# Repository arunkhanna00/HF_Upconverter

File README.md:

# Upconverter
An upconverter used to convert HF signals (3-33 MHz) to 125+MHz that can be recognized by an RTL-SDR

Inspired by [Nooelectric Ham It Up](https://www.nooelec.com/store/ham-it-up.html)

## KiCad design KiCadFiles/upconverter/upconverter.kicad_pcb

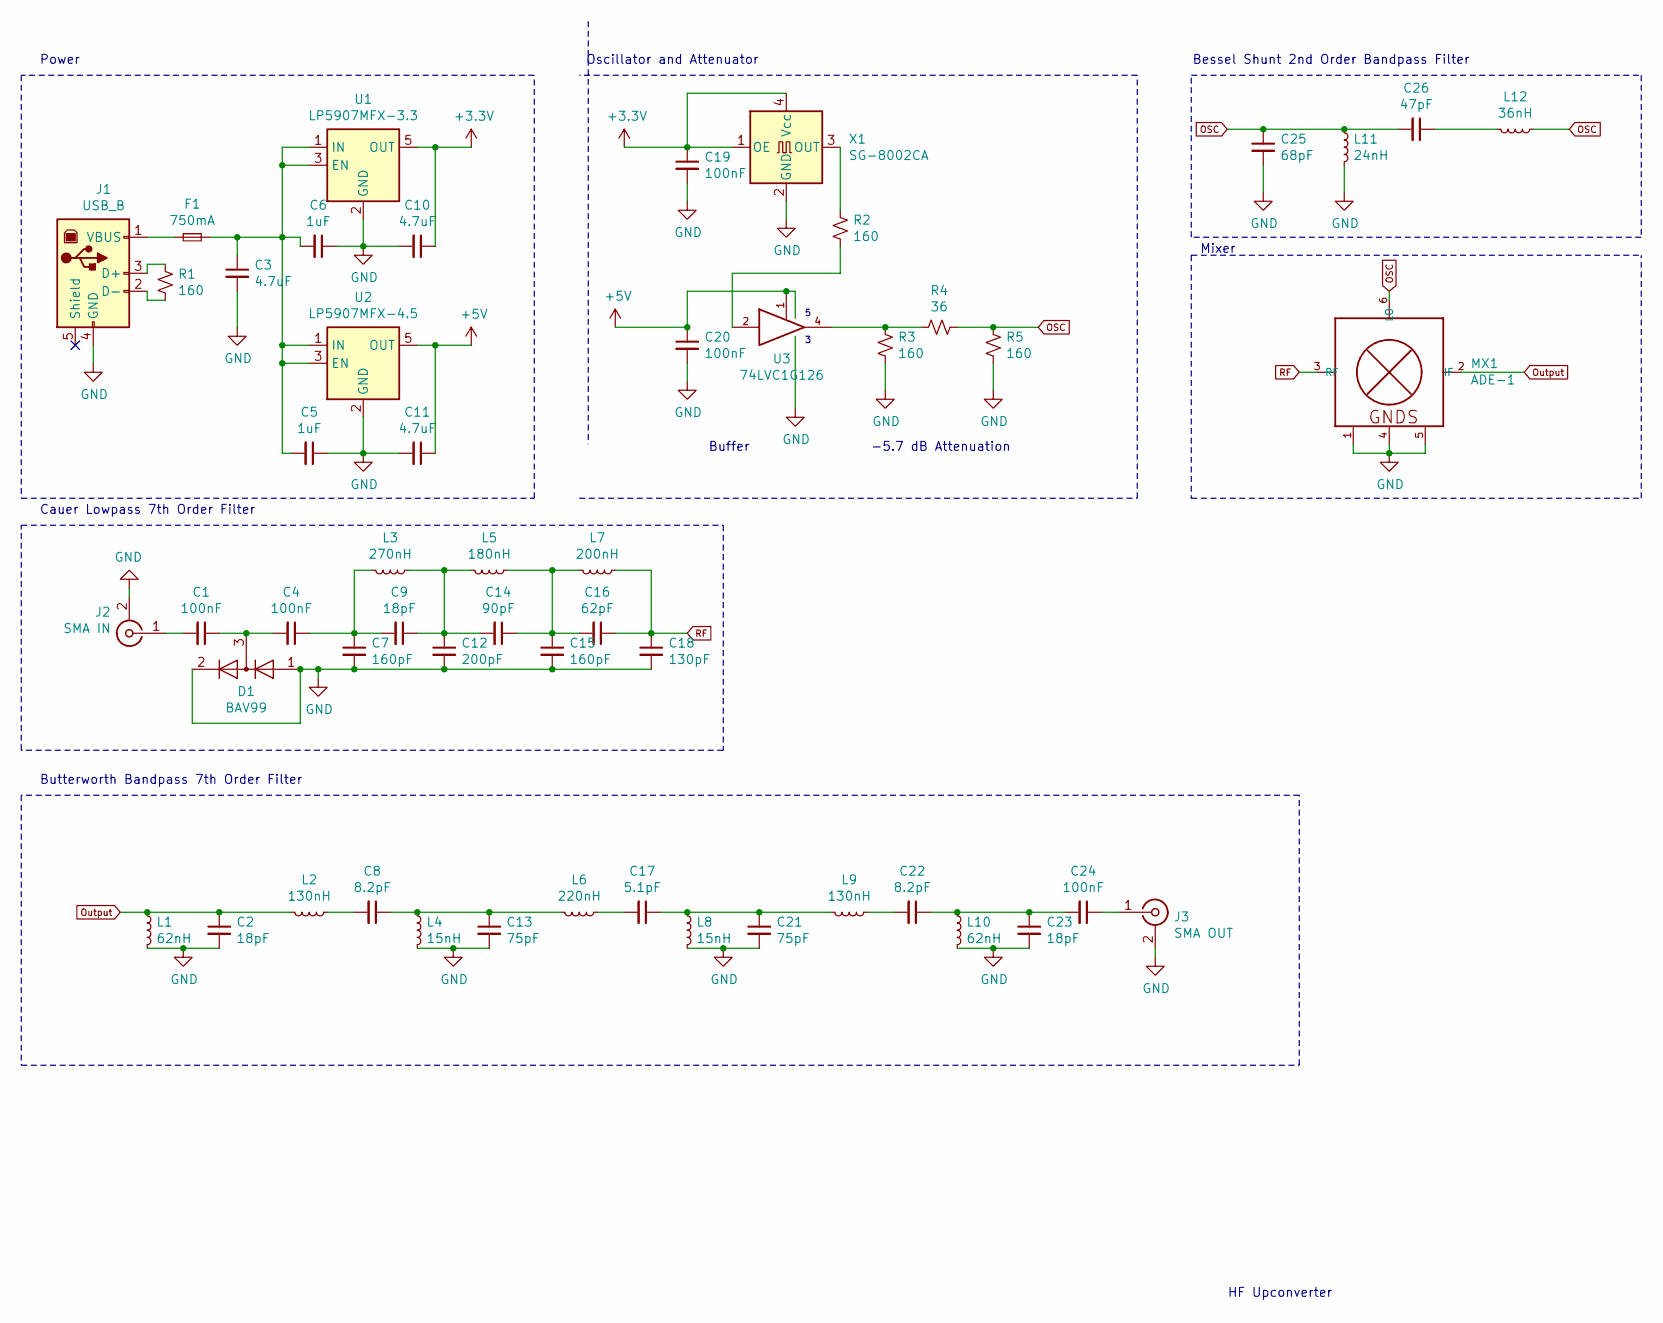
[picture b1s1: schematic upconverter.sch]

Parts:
C1, C4, C19, C20, C24: 100nF; C_0805_2012Metric
C2, C9, C23: 18pF; C_0805_2012Metric
C3, C10, C11: 4.7uF; C_0805_2012Metric
C5, C6: 1uF; C_0805_2012Metric
C7, C15: 160pF; C_0805_2012Metric
C8, C22: 8.2pF; C_0805_2012Metric
C12: 200pF; C_0805_2012Metric
C13, C21: 75pF; C_0805_2012Metric
C14: 90pF; C_0805_2012Metric
C16: 62pF; C_0805_2012Metric
C17: 5.1pF; C_0805_2012Metric
C18: 130pF; C_0805_2012Metric
C25: 68pF; C_0805_2012Metric
C26: 47pF; C_0805_2012Metric
D1: BAV99; SOT-23
F1: 750mA; Fuse_1206_3216Metric_Castellated
J1: USB_B; USB_B_OST_USB-B1HSxx_Horizontal
J2: SMA IN; SMA_Samtec_SMA-J-P-X-ST-EM1_EdgeMount
J3: SMA OUT; SMA_Samtec_SMA-J-P-X-ST-EM1_EdgeMount
L1, L10: 62nH; L_0805_2012Metric
L2, L9: 130nH; L_0805_2012Metric
L3: 270nH; L_0805_2012Metric
L4, L8: 15nH; L_0805_2012Metric
L5: 180nH; L_0805_2012Metric
L6: 220nH; L_0805_2012Metric
L7: 200nH; L_0805_2012Metric
L11: 24nH; L_0805_2012Metric
L12: 36nH; L_0805_2012Metric
MX1: ADE-1; CD636
R1, R2, R3, R5: 160; R_0805_2012Metric
R4: 36; R_0805_2012Metric
U1: LP5907MFX-3.3; SOT-23-5
U2: LP5907MFX-4.5; SOT-23-5
U3: 74LVC1G126; SOT-23-5
X1: SG-8002CA; Oscillator_SMD_SeikoEpson_SG8002CA-4Pin_7.0x5.0mm

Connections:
+3V3: C10.1, C19.1, U1.5 (OUT), X1.1 (OE), X1.4 (Vcc)
+5V: C11.1, C20.1, U2.5 (OUT), U3.1, U3.5 (VCC)
GND: C2.2, C3.2, C5.1, C6.1, C7.2, C10.2, C11.2, C12.2, C13.2, C15.2, C18.2, C19.2, C20.2, C21.2, C23.2, C25.2, D1.1 (K), D1.2 (A), J1.4 (GND), J2.2 (Ext), J3.2 (Ext), L1.2, L4.2, L8.2, L10.2, L11.2, MX1.1, MX1.4, MX1.5, R3.2, R5.2, U1.2 (GND), U2.2 (GND), U3.3 (GND), X1.2 (GND)
unnamed: C1.1, C4.2, D1.3 (K)
unnamed: C1.2, J2.1 (In)
unnamed: C3.1, C5.2, C6.2, F1.2, U1.1 (IN), U1.3 (EN), U2.1 (IN), U2.3 (EN)
unnamed: C4.1, C7.1, C9.2, L3.2
unnamed: C8.2, L2.1
unnamed: C9.1, C12.1, C14.2, L3.1, L5.2
unnamed: C8.1, C13.1, L4.1, L6.2
unnamed: C14.1, C15.1, C16.2, L5.1, L7.2
unnamed: C17.1, C21.1, L8.1, L9.2
unnamed: C17.2, L6.1
unnamed: C22.1, C23.1, C24.2, L10.1
unnamed: C22.2, L9.1
unnamed: C24.1, J3.1 (In)
unnamed: C26.1, L12.2
unnamed: F1.1, J1.1 (VBUS)
unnamed: J1.2 (D-), R1.2
unnamed: J1.3 (D+), R1.1
unnamed: R2.1, X1.3 (OUT)
unnamed: R2.2, U3.2
unnamed: R3.1, R4.2, U3.4
OSC: C25.1, C26.2, L11.1, L12.1, MX1.6 (LO), R4.1, R5.1
Output: C2.1, L1.1, L2.2, MX1.2 (IF)
RF: C16.1, C18.1, L7.1, MX1.3 (RF)

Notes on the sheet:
HF Upconverter
Power
Oscillator and Attenuator
-5.7 dB Attenuation
Mixer
Buffer
Cauer Lowpass 7th Order Filter
Butterworth Bandpass 7th Order Filter
Bessel Shunt 2nd Order Bandpass Filter

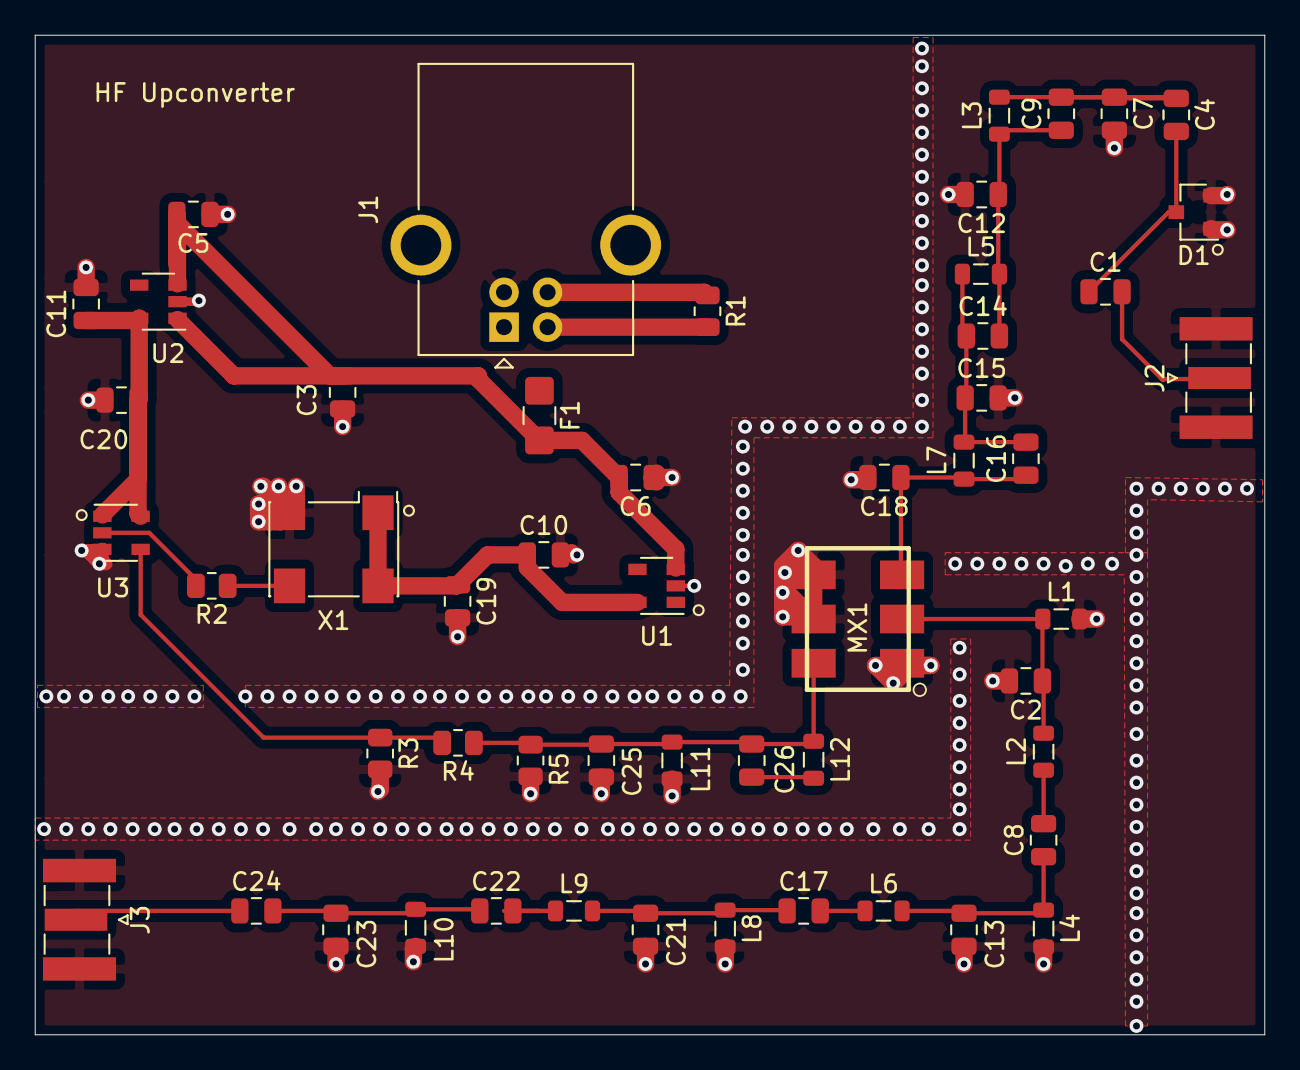
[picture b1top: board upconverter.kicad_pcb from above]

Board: 2 copper layers, 70.6 x 57.4 mm, 53 parts (0 on the bottom side), 26 nets.

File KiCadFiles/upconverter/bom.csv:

"Id";"Designator";"Package";"Quantity";"Designation";"Supplier and ref";
1;"J2";"SMA_Samtec_SMA-J-P-X-ST-EM1_EdgeMount";1;"SMA IN";;;
2;"J3";"SMA_Samtec_SMA-J-P-X-ST-EM1_EdgeMount";1;"SMA OUT";;;
3;"C20,C1,C4,C19,C24";"C_0805_2012Metric";5;"100nF";;;
4;"C2,C9,C23";"C_0805_2012Metric";3;"18pF";;;
5;"C3,C10,C11";"C_0805_2012Metric";3;"4.7uF";;;
6;"C5,C6";"C_0805_2012Metric";2;"1uF";;;
7;"C7,C15";"C_0805_2012Metric";2;"160pF";;;
8;"C8,C22";"C_0805_2012Metric";2;"8.2pF";;;
9;"C12";"C_0805_2012Metric";1;"200pF";;;
10;"C13,C21";"C_0805_2012Metric";2;"75pF";;;
11;"C14";"C_0805_2012Metric";1;"90pF";;;
12;"C16";"C_0805_2012Metric";1;"62pF";;;
13;"C17";"C_0805_2012Metric";1;"5.1pF";;;
14;"C18";"C_0805_2012Metric";1;"130pF";;;
15;"C25";"C_0805_2012Metric";1;"68pF";;;
16;"C26";"C_0805_2012Metric";1;"47pF";;;
17;"D1";"SOT-23";1;"BAV99";;;
18;"F1";"Fuse_1206_3216Metric_Castellated";1;"750mA";;;
19;"J1";"USB_B_OST_USB-B1HSxx_Horizontal";1;"USB_B";;;
20;"L1,L10";"L_0805_2012Metric";2;"62nH";;;
21;"L2,L9";"L_0805_2012Metric";2;"130nH";;;
22;"L3";"L_0805_2012Metric";1;"270nH";;;
23;"L4,L8";"L_0805_2012Metric";2;"15nH";;;
24;"L5";"L_0805_2012Metric";1;"180nH";;;
25;"L6";"L_0805_2012Metric";1;"220nH";;;
26;"L7";"L_0805_2012Metric";1;"200nH";;;
27;"L11";"L_0805_2012Metric";1;"24nH";;;
28;"L12";"L_0805_2012Metric";1;"36nH";;;
29;"MX1";"CD636";1;"ADE-1";;;
30;"R1,R2,R3,R5";"R_0805_2012Metric";4;"160";;;
31;"R4";"R_0805_2012Metric";1;"36";;;
32;"U1";"SOT-23-5";1;"LP5907MFX-3.3";;;
33;"U2";"SOT-23-5";1;"LP5907MFX-4.5";;;
34;"U3";"SOT-23-5";1;"74LVC1G126";;;
35;"X1";"Oscillator_SMD_SeikoEpson_SG8002CA-4Pin_7.0x5.0mm";1;"SG-8002CA";;;

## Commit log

2021-08-21 Add gerber files
2021-08-21 Add schematic
2021-08-21 s-params of filters
    Used Elsie to calculate these
